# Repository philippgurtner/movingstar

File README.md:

# Movingstar
SwissSkills Homework 2020

Dieses Projekt dient als Hausaufgabe für die Vorselektion.
Mein persönliches Ziel ist es, die Schweizermesterschaft mit FOSS (Free Open Source Software) zu bestreiten.

## Toolchain
- [KiCad](https://github.com/KiCad) -> ECAD: Schema & Layout
- Python -> Berechnungen: Stern z.B.

## Hardware

### Lichtsensor & ADC
I(10klx) = 1mA
I(100lx) = 23uA
VCC = 5V
=> R=5k
U(10klx) = I*R = 1mA * 5k = 5V
U(100lx) = I*R = 23uA * 5k = 115mV

### I2C Levelshifter
U104 (Bewegung Sensor) wird mit 2.5V - 3V versorgt. Das I2C Signal bei 2.5V Versorgung genügt dem Microcontroller (U102) nicht für ein logisches 1 (0.7 * VCC = 0.7 * 5V = 3.5V)
So muss das Signal geshiftet werden.
Dies geschieht nach [NXP AN10441](https://www.nxp.com/docs/en/application-note/AN10441.pdf) über die beiden Mosfets Q102 & Q103.

### Programmieren
Als Programmierschnittstelle wird die UPDI Schnittstelle von Atmel verwendet. Diese kommt mit einem Pin aus.

### Stromversorgung
Die Stromversorgung wurde über eine USB-C Buchse vorgesehen. Es stehen dann ca. 5V von einem Handelsüblichen Steckernetzteil zur Verfügung.
Imax ~= 30LED * 3Farben * ca. 20mA = 1.8A
Somit sollte die Quelle auf 2A ausgelegt werden um alle LEDs komplett anzusteuern.
Für die Versorgung von U104 Steht ein 3.3V (oder auch 2.5V) Spannungsregler U101 zur Verfügung.
Der Microcontroller U102 wird nicht mit 3.3V Versorgt, da sonst die Taktfrequenz gesenkt werden muss. Dies wurde zum Enwicklungszeitpunkt noch nicht gemacht, um alle Möglichkeiten der LED (WS2812B-2020) Ansteuerung offen zu halten.

### LED Ansteuerung

Als LED Ansteuerung wurden mehrere Möglichkeiten offen gelassen.
- SPI Interface MOSI an PA1 (R105 bestückt)
- I2C Interface SDA an PA1 (R105 bestückt)
- Waveform Generator Output WO3 an PA3 (R106 bestückt)

### Accelerometer U104

Der Beschleunigungssensor wird über I2C über den Levelshifter betrieben. Die Interruptpins können optional verwendet werden.
Die Interrupt Pins müssten auch über einen Levelshifter betrieben werden um eine Korrekte Funktion beim Microcontroller zu erzeugen.

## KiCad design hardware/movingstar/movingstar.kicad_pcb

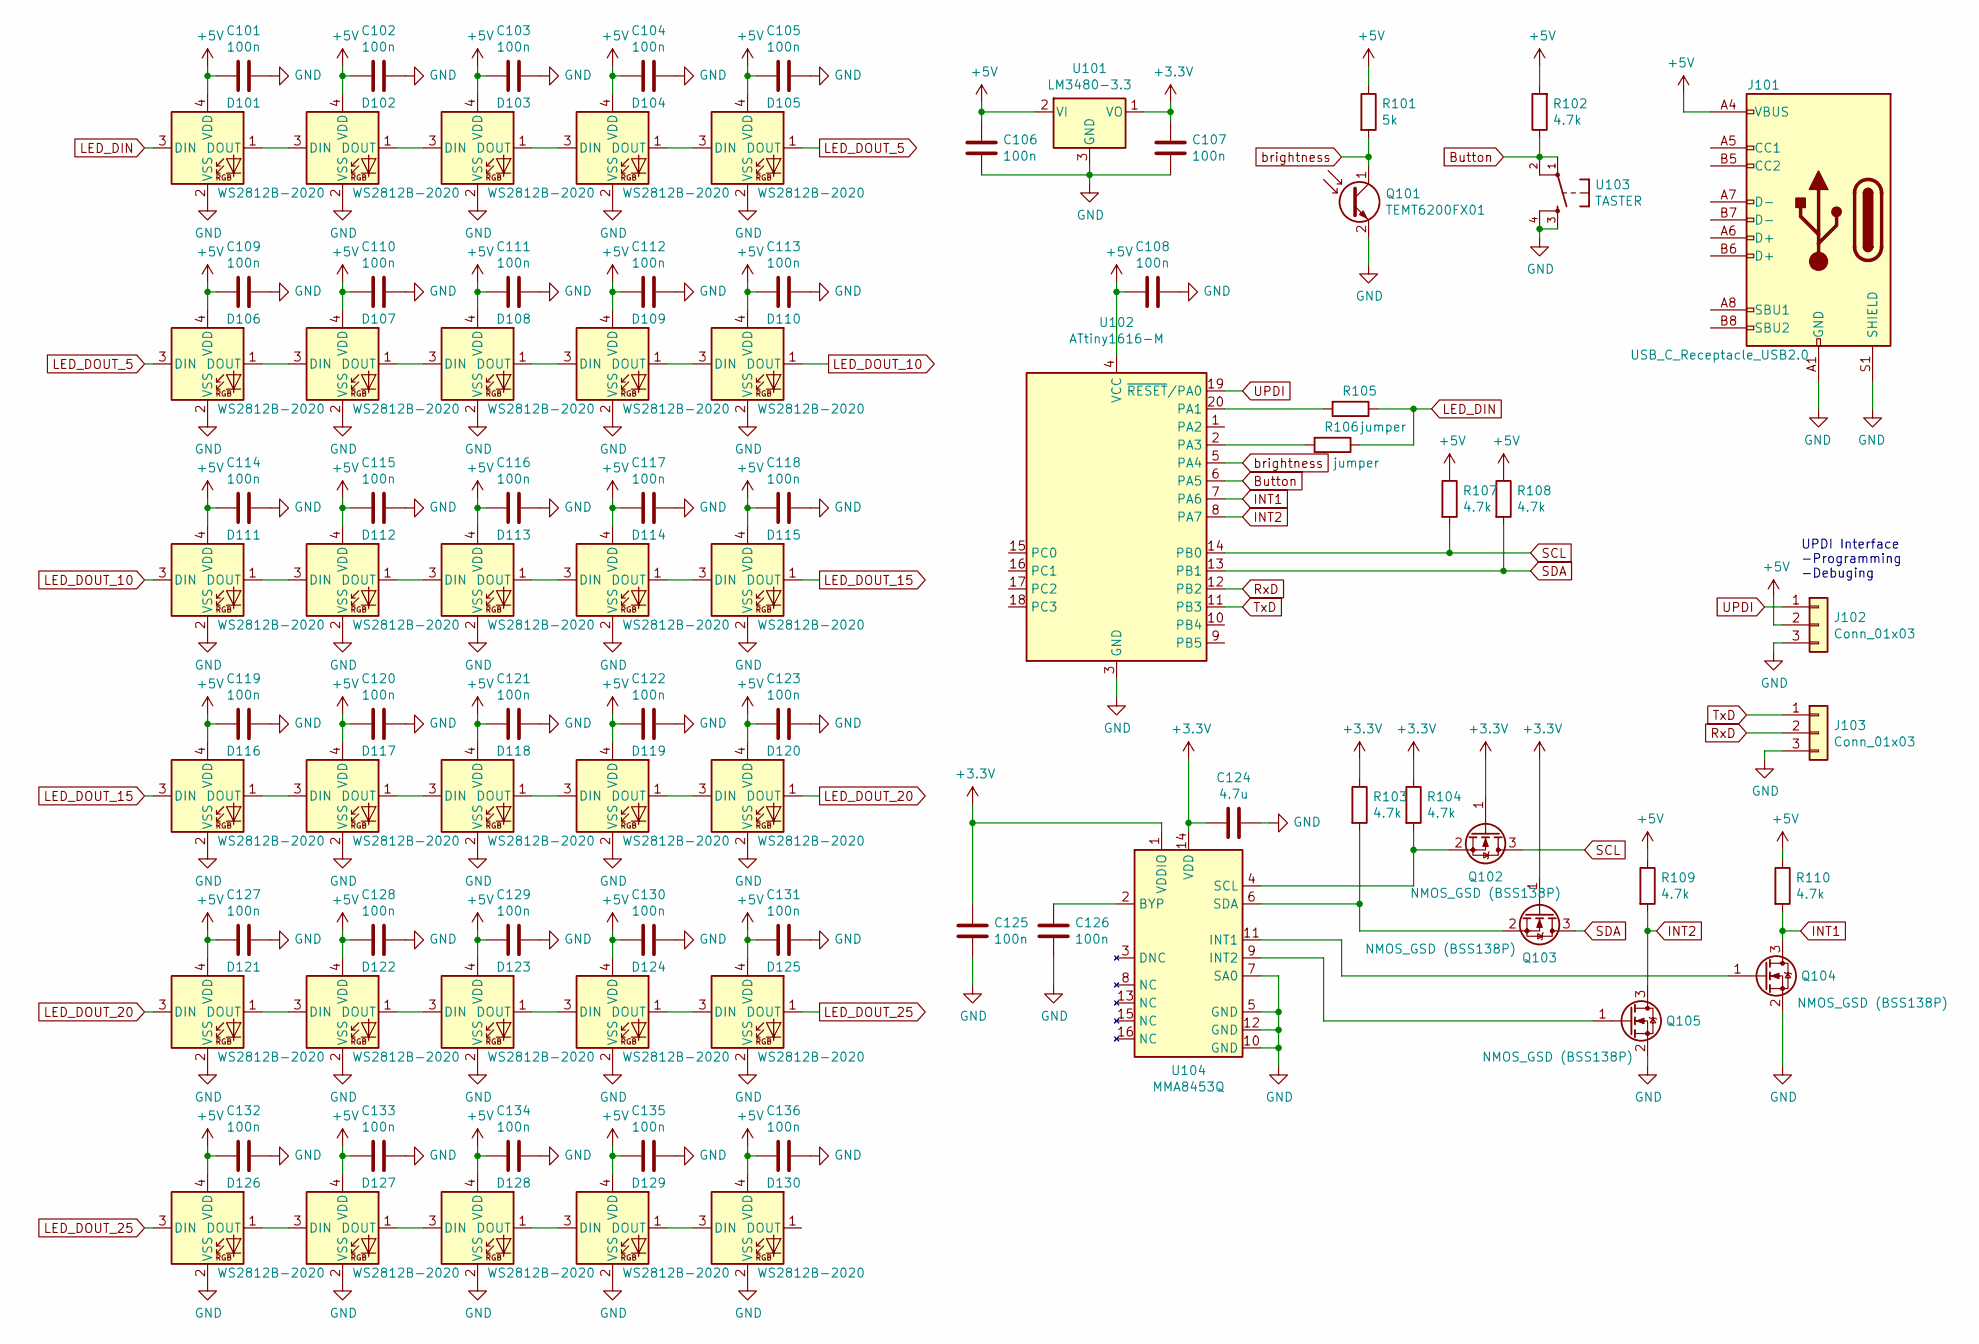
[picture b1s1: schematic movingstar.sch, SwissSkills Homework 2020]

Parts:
C101, C102, C103, C104, C105, C106, C107, C108, C109, C110, C111, C112, C113, C114, C115, C116, C117, C118, C119, C120, C121, C122, C123, C125, C126, C127, C128, C129, C130, C131, C132, C133, C134, C135, C136: 100n; C_0603_1608Metric
C124: 4.7u; C_0603_1608Metric
D101, D102, D103, D104, D105, D106, D107, D108, D109, D110, D111, D112, D113, D114, D115, D116, D117, D118, D119, D120, D121, D122, D123, D124, D125, D126, D127, D128, D129, D130: WS2812B-2020
J101: USB_C_Receptacle_USB2.0; USB_C_Molex_fyang05
J102, J103: Conn_01x03; PinHeader_1x03_P2.54mm_Vertical
Q101: TEMT6200FX01; R_0805_2012Metric
Q102, Q103, Q104, Q105: NMOS_GSD (BSS138P); SOT-23
R101: 5k; R_0603_1608Metric
R102, R103, R104, R107, R108, R109, R110: 4.7k; R_0603_1608Metric
R105, R106: jumper; R_0603_1608Metric
U101: LM3480-3.3; SOT-23
U102: ATtiny1616-M; VQFN-20-1EP_3x3mm_P0.4mm_EP1.7x1.7mm
U103: TASTER
U104: MMA8453Q; QFN-16-1EP_3x3mm_P0.5mm_EP1.7x1.7mm

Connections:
+3V3: C107.1, C124.2, C125.1, Q102.1 (G), Q103.1 (G), R103.1, R104.1, U101.1 (VO), U104.1 (VDDIO), U104.14 (VDD)
+5V: C101.2, C102.2, C103.2, C104.2, C105.2, C106.1, C108.2, C109.2, C110.2, C111.2, C112.2, C113.2, C114.2, C115.2, C116.2, C117.2, C118.2, C119.2, C120.2, C121.2, C122.2, C123.2, C127.2, C128.2, C129.2, C130.2, C131.2, C132.2, C133.2, C134.2, C135.2, C136.2, D101.4 (VDD), D102.4 (VDD), D103.4 (VDD), D104.4 (VDD), D105.4 (VDD), D106.4 (VDD), D107.4 (VDD), D108.4 (VDD), D109.4 (VDD), D110.4 (VDD), D111.4 (VDD), D112.4 (VDD), D113.4 (VDD), D114.4 (VDD), D115.4 (VDD), D116.4 (VDD), D117.4 (VDD), D118.4 (VDD), D119.4 (VDD), D120.4 (VDD), D121.4 (VDD), D122.4 (VDD), D123.4 (VDD), D124.4 (VDD), D125.4 (VDD), D126.4 (VDD), D127.4 (VDD), D128.4 (VDD), D129.4 (VDD), D130.4 (VDD), J101.A4 (VBUS), J101.A9 (VBUS), J101.B4 (VBUS), J101.B9 (VBUS), J102.2, R101.1, R102.2, R107.1, R108.1, R109.1, R110.1, U101.2 (VI), U102.4 (VCC)
Button: R102.1, U102.6 (PA5), U103.1, U103.2 (P1)
GND: C101.1, C102.1, C103.1, C104.1, C105.1, C106.2, C107.2, C108.1, C109.1, C110.1, C111.1, C112.1, C113.1, C114.1, C115.1, C116.1, C117.1, C118.1, C119.1, C120.1, C121.1, C122.1, C123.1, C124.1, C125.2, C126.2, C127.1, C128.1, C129.1, C130.1, C131.1, C132.1, C133.1, C134.1, C135.1, C136.1, D101.2 (VSS), D102.2 (VSS), D103.2 (VSS), D104.2 (VSS), D105.2 (VSS), D106.2 (VSS), D107.2 (VSS), D108.2 (VSS), D109.2 (VSS), D110.2 (VSS), D111.2 (VSS), D112.2 (VSS), D113.2 (VSS), D114.2 (VSS), D115.2 (VSS), D116.2 (VSS), D117.2 (VSS), D118.2 (VSS), D119.2 (VSS), D120.2 (VSS), D121.2 (VSS), D122.2 (VSS), D123.2 (VSS), D124.2 (VSS), D125.2 (VSS), D126.2 (VSS), D127.2 (VSS), D128.2 (VSS), D129.2 (VSS), D130.2 (VSS), J101.A1 (GND), J101.A12 (GND), J101.B1 (GND), J101.B12 (GND), J101.S1 (SHIELD), J102.3, J103.3, Q101.2 (E), Q104.2 (S), Q105.2 (S), U101.3 (GND), U102.3 (GND), U102.21 (GND), U103.3 (S), U103.4 (S1), U104.5 (GND), U104.7 (SA0), U104.10 (GND), U104.12 (GND)
INT1: Q104.3 (D), R110.2, U102.7 (PA6)
INT2: Q105.3 (D), R109.2, U102.8 (PA7)
LED_DIN: D101.3 (DIN), R105.1, R106.1
LED_DOUT_5: D105.1 (DOUT), D106.3 (DIN)
LED_DOUT_10: D110.1 (DOUT), D111.3 (DIN)
LED_DOUT_15: D115.1 (DOUT), D116.3 (DIN)
LED_DOUT_20: D120.1 (DOUT), D121.3 (DIN)
LED_DOUT_25: D125.1 (DOUT), D126.3 (DIN)
unnamed: C126.1, U104.2 (BYP)
unnamed: D101.1 (DOUT), D102.3 (DIN)
unnamed: D102.1 (DOUT), D103.3 (DIN)
unnamed: D103.1 (DOUT), D104.3 (DIN)
unnamed: D104.1 (DOUT), D105.3 (DIN)
unnamed: D106.1 (DOUT), D107.3 (DIN)
unnamed: D107.1 (DOUT), D108.3 (DIN)
unnamed: D108.1 (DOUT), D109.3 (DIN)
unnamed: D109.1 (DOUT), D110.3 (DIN)
unnamed: D111.1 (DOUT), D112.3 (DIN)
unnamed: D112.1 (DOUT), D113.3 (DIN)
unnamed: D113.1 (DOUT), D114.3 (DIN)
unnamed: D114.1 (DOUT), D115.3 (DIN)
unnamed: D116.1 (DOUT), D117.3 (DIN)
unnamed: D117.1 (DOUT), D118.3 (DIN)
unnamed: D118.1 (DOUT), D119.3 (DIN)
unnamed: D119.1 (DOUT), D120.3 (DIN)
unnamed: D121.1 (DOUT), D122.3 (DIN)
unnamed: D122.1 (DOUT), D123.3 (DIN)
unnamed: D123.1 (DOUT), D124.3 (DIN)
unnamed: D124.1 (DOUT), D125.3 (DIN)
unnamed: D126.1 (DOUT), D127.3 (DIN)
unnamed: D127.1 (DOUT), D128.3 (DIN)
unnamed: D128.1 (DOUT), D129.3 (DIN)
unnamed: D129.1 (DOUT), D130.3 (DIN)
unnamed: Q102.2 (S), R104.2, U104.4 (SCL)
unnamed: Q103.2 (S), R103.2, U104.6 (SDA)
unnamed: Q104.1 (G), U104.11 (INT1)
unnamed: Q105.1 (G), U104.9 (INT2)
unnamed: R105.2, U102.20 (PA1)
unnamed: R106.2, U102.2 (PA3)
RxD: J103.2, U102.12 (PB2)
SCL: Q102.3 (D), R107.2, U102.14 (PB0)
SDA: Q103.3 (D), R108.2, U102.13 (PB1)
TxD: J103.1, U102.11 (PB3)
UPDI: J102.1, U102.19 (~RESET~/PA0)
brightness: Q101.1 (C), R101.2, U102.5 (PA4)

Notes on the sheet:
UPDI Interface -Programming -Debuging

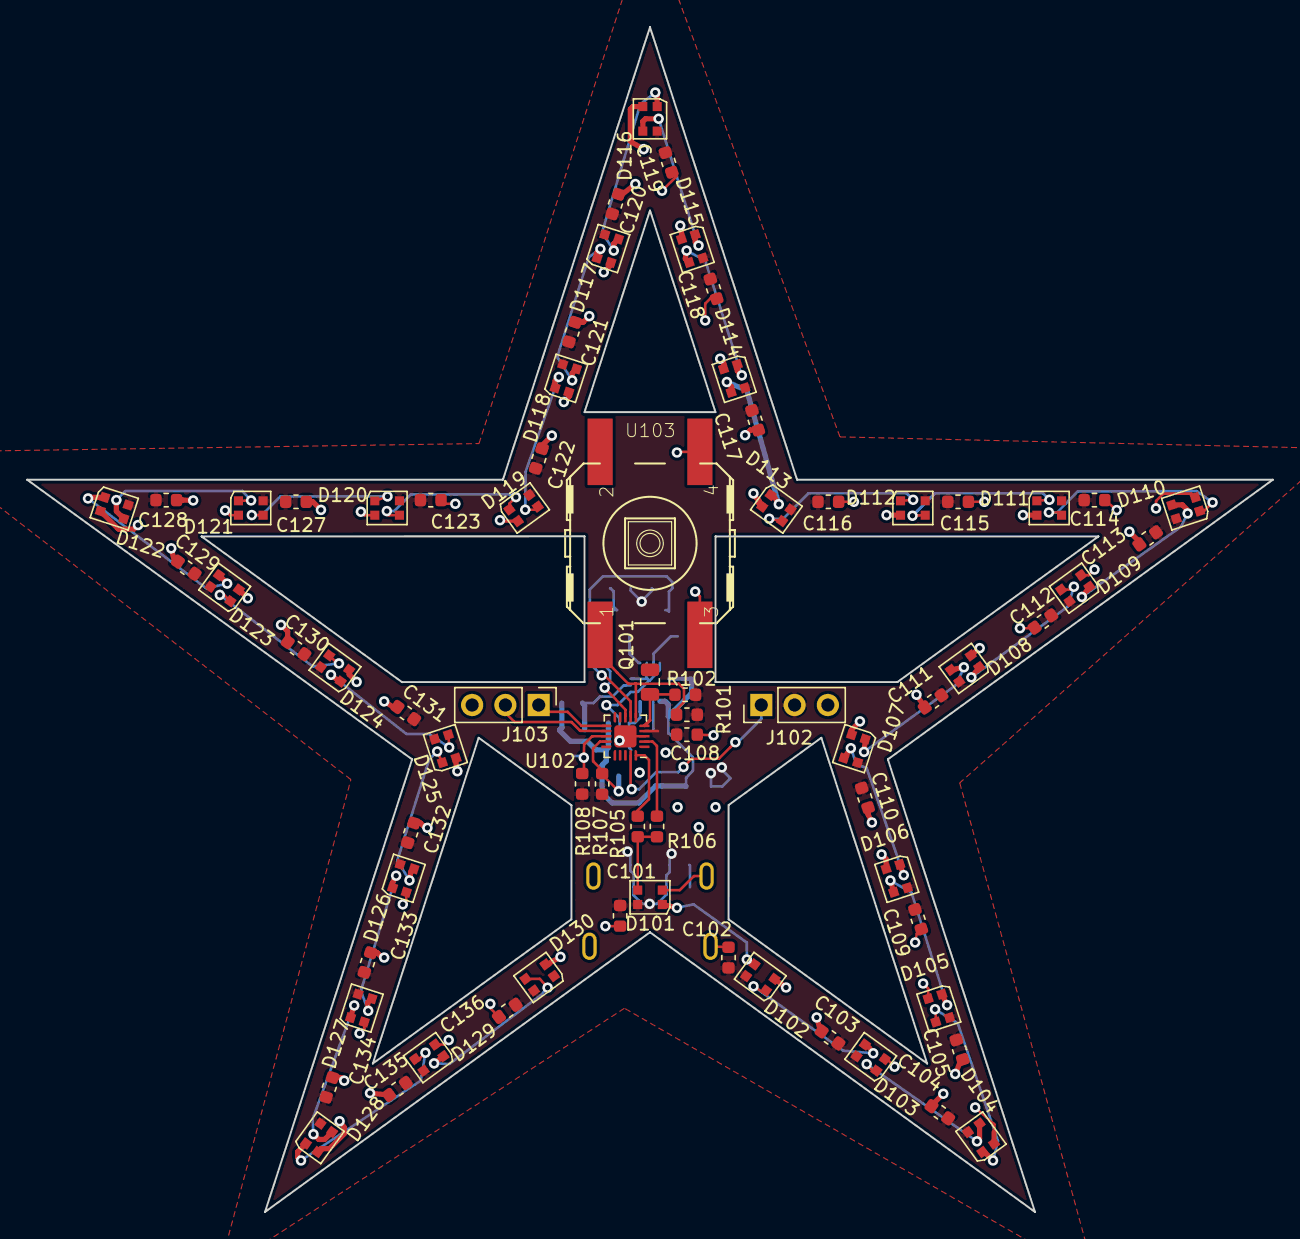
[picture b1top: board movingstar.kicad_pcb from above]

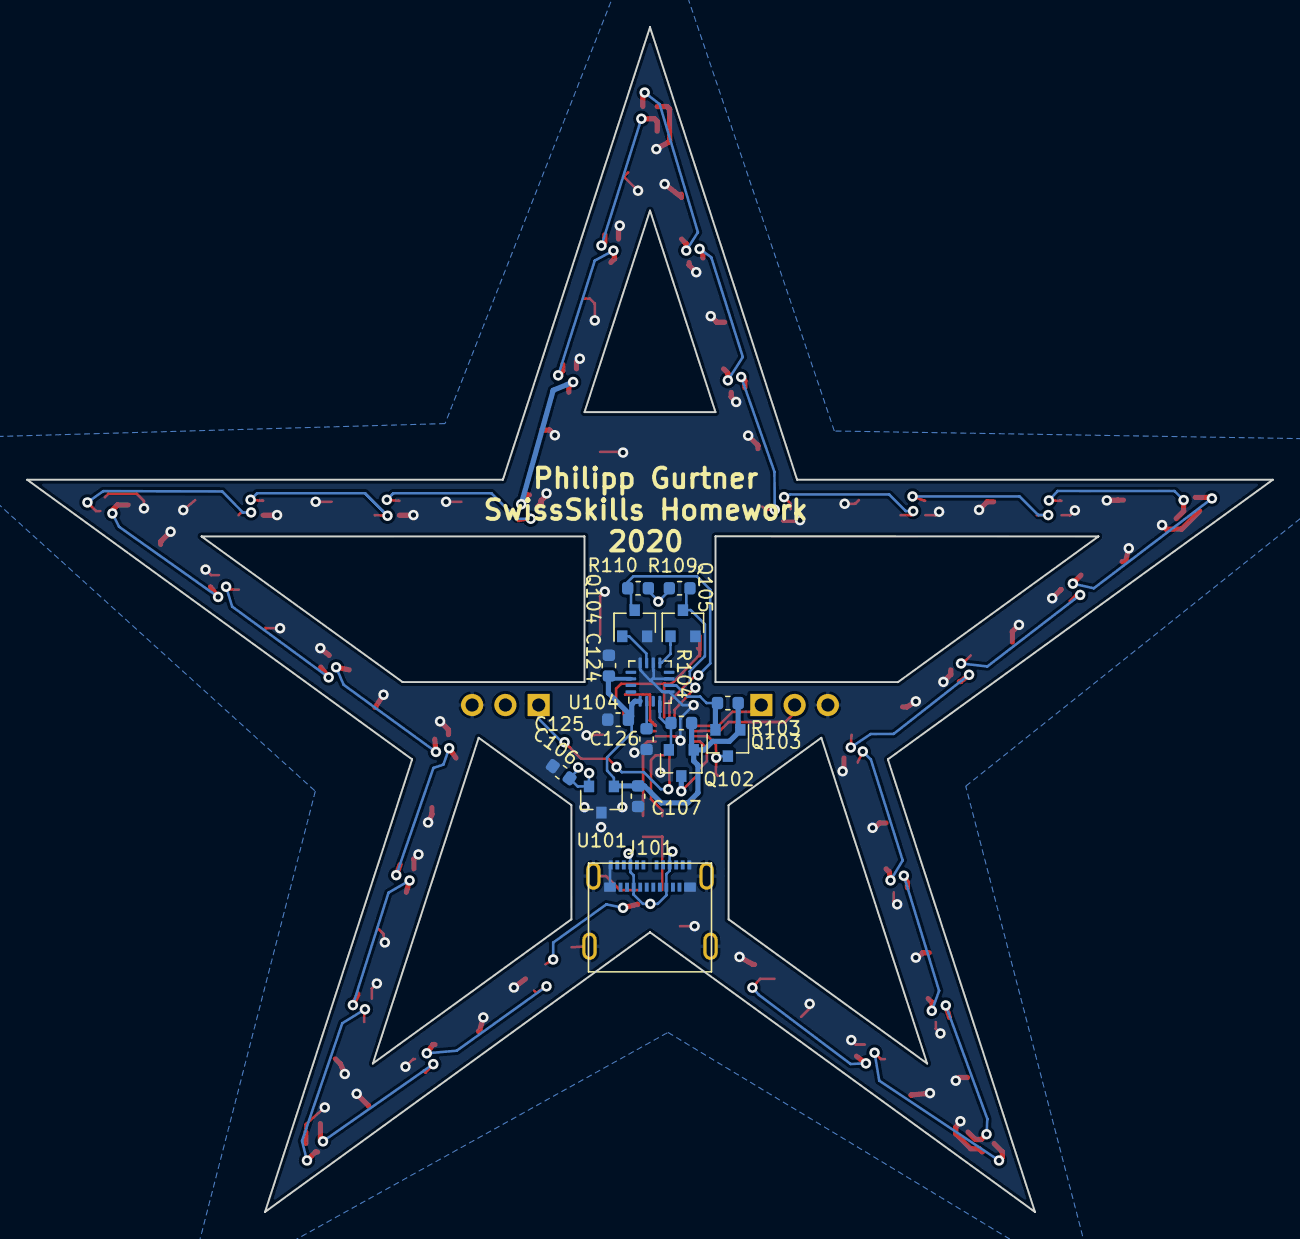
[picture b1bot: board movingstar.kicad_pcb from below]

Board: 2 copper layers, 95.1 x 90.4 mm, 88 parts (16 on the bottom side), 49 nets.

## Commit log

2020-04-28 the first commit
